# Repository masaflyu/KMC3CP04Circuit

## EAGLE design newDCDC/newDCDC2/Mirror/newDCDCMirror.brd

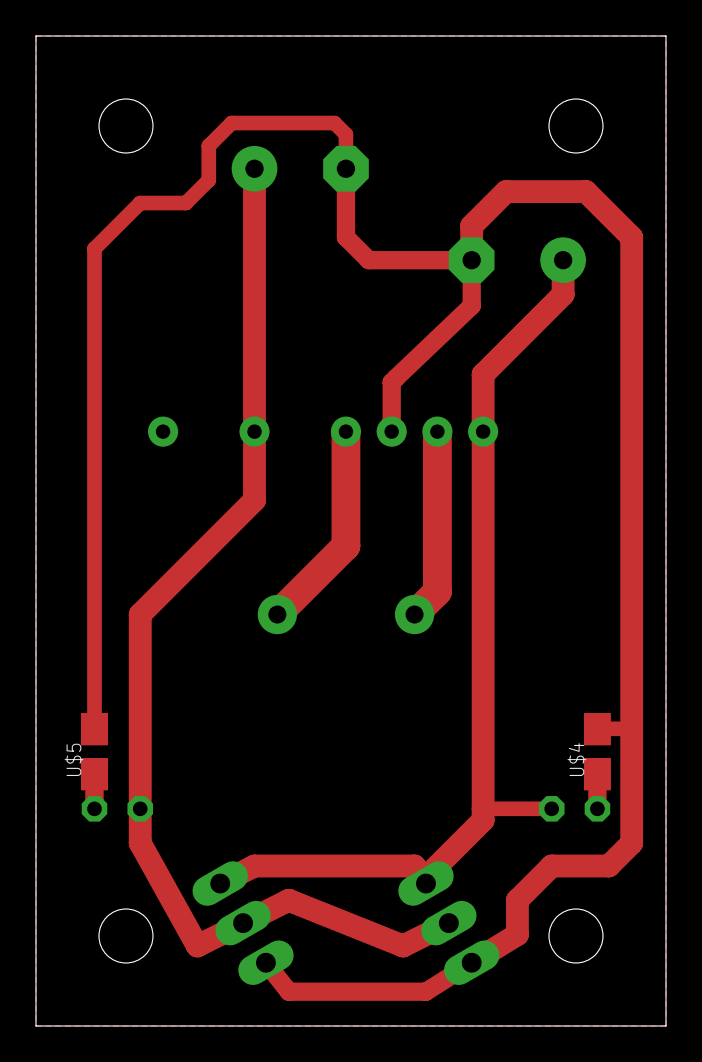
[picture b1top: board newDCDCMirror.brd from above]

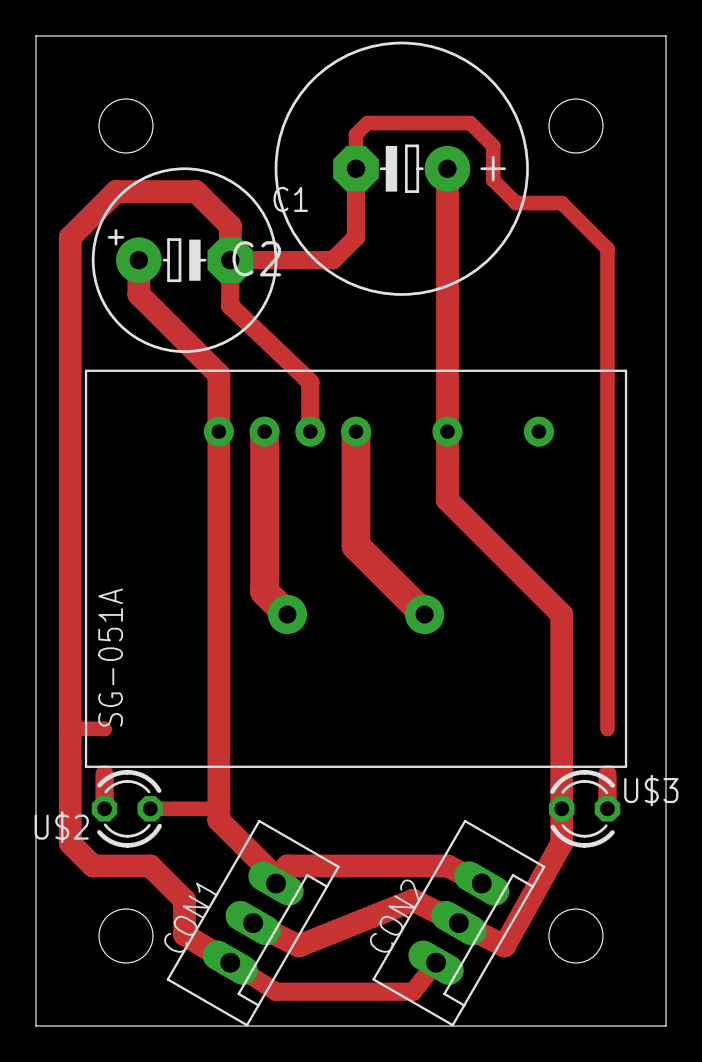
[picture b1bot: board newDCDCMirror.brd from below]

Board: 2 copper layers, 35.0 x 55.0 mm, 9 parts (7 on the bottom side), 7 nets.

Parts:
C1: 50V470uF; D=2,φ=10,5
C2: 35V1000uF; D=2,φ=13
CON1, CON2: CON3
U$1: SG-051A
U$2, U$3: LED(砲弾型)3; LED3MM
U$4: 4.7k; 0805
U$5: 1k; 0805

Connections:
+5V: C2.+, CON1.P$2, CON2.P$2, U$1.P$5, U$3.A
+24V: C1.+, CON1.P$1, CON2.P$1, U$1.P$1, U$2.A
GND: C1.-, C2.-, CON1.P$3, CON2.P$3, U$1.P$3, U$4.2, U$5.2
unnamed: U$1.P$4, U$1.P$7
unnamed: U$1.P$2, U$1.P$8
unnamed: U$2.K, U$4.1
unnamed: U$3.K, U$5.1
